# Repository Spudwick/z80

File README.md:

# z80

Repository for all things related to z80 project. Makefile supports both windows and linux!

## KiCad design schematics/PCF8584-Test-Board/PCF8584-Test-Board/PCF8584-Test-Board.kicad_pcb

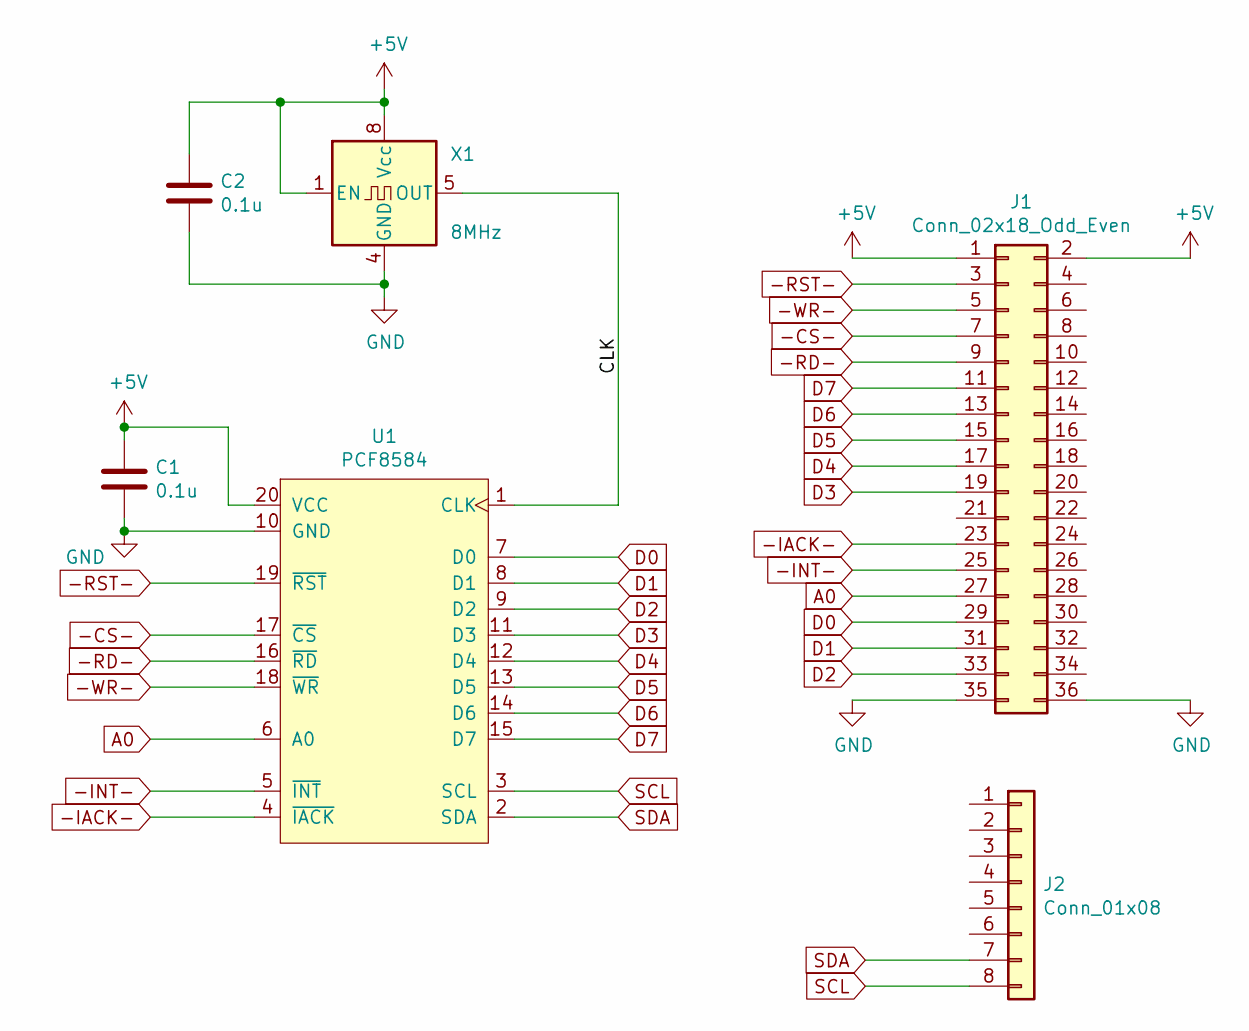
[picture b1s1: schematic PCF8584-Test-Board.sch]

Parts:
C1, C2: 0.1u; C_0603_1608Metric_Pad1.05x0.95mm_HandSolder
J1: Conn_02x18_Odd_Even; PinHeader_2x18_P2.54mm_Vertical
J2: Conn_01x08; PinHeader_1x08_P2.54mm_Vertical
U1: PCF8584; SOIC-20W_7.5x12.8mm_P1.27mm
X1: 8MHz; Oscillator_DIP-8

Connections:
+5V: C1.1, C2.1, J1.1, J1.2, U1.20 (VCC), X1.1 (EN), X1.8 (Vcc)
-CS-: J1.7, U1.17 (~CS)
-IACK-: J1.23, U1.4 (~IACK)
-INT-: J1.25, U1.5 (~INT)
-RD-: J1.9, U1.16 (~RD)
-RST-: J1.3, U1.19 (~RST)
-WR-: J1.5, U1.18 (~WR)
/CLK: U1.1 (CLK), X1.5 (OUT)
A0: J1.27, U1.6 (A0)
D0: J1.29, U1.7 (D0)
D1: J1.31, U1.8 (D1)
D2: J1.33, U1.9 (D2)
D3: J1.19, U1.11 (D3)
D4: J1.17, U1.12 (D4)
D5: J1.15, U1.13 (D5)
D6: J1.13, U1.14 (D6)
D7: J1.11, U1.15 (D7)
GND: C1.2, C2.2, J1.35, J1.36, U1.10 (GND), X1.4 (GND)
SCL: J2.8, U1.3 (SCL)
SDA: J2.7, U1.2 (SDA)

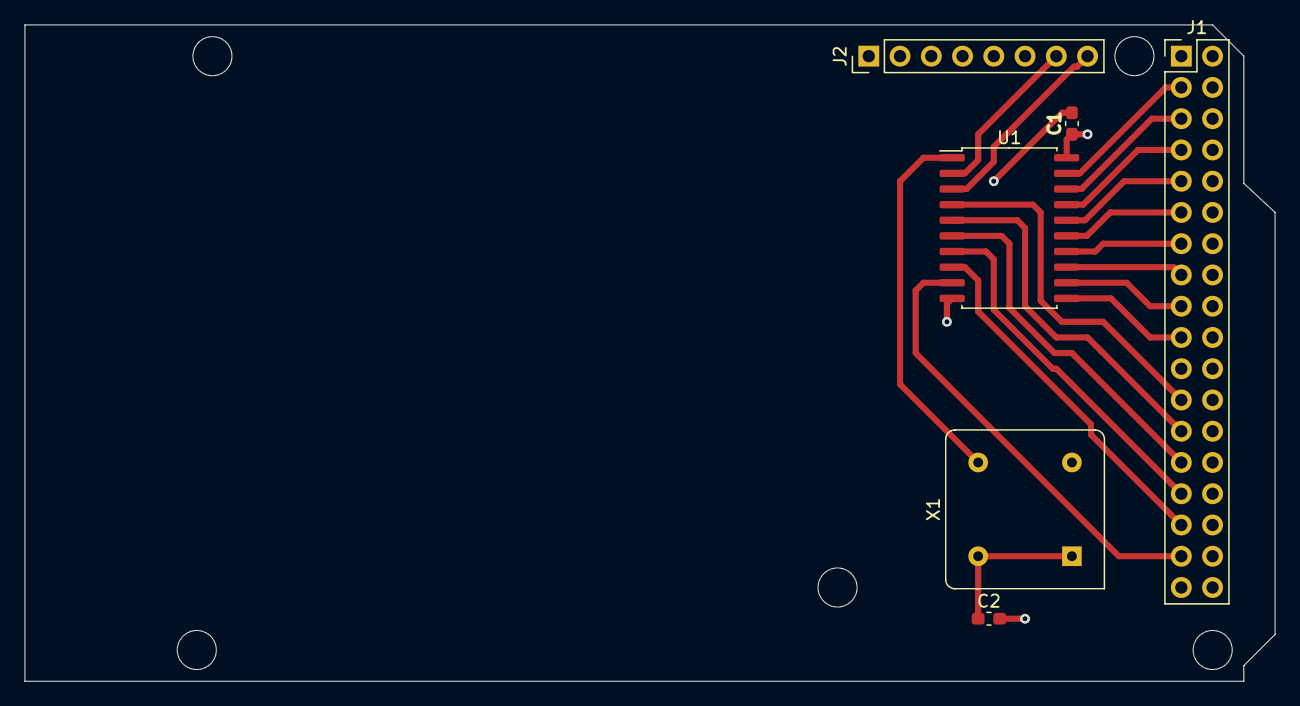
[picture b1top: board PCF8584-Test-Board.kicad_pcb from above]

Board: 2 copper layers, 101.6 x 53.3 mm, 6 parts (0 on the bottom side), 20 nets.

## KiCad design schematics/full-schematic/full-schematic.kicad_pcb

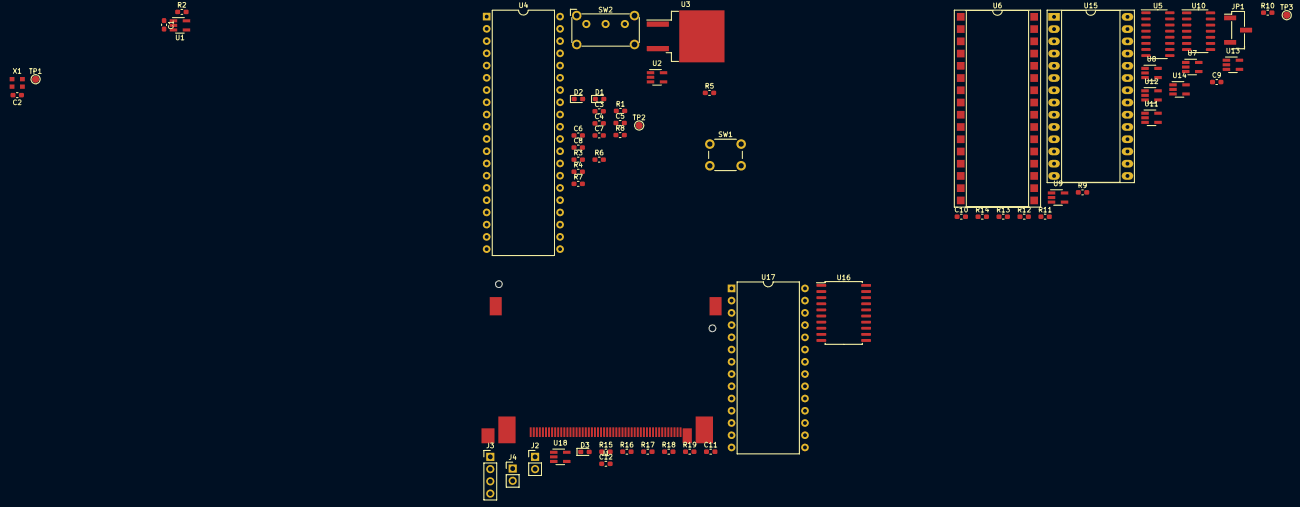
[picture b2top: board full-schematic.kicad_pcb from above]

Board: 2 copper layers, 63 parts (0 on the bottom side), 77 nets, no tracks yet.

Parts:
C1, C2, C3, C4, C7, C8, C9, C10, C11, C12: 0.1u; C_0603_1608Metric_Pad1.05x0.95mm_HandSolder
C5, C6: 1m; C_0603_1608Metric_Pad1.05x0.95mm_HandSolder
D1: D_Schottky; D_0603_1608Metric_Pad1.05x0.95mm_HandSolder
D2, D3: LED; LED_0603_1608Metric_Pad1.05x0.95mm_HandSolder
J1: Conn_02x25_Top_Bottom; Molex_553595029_CF_Socket
J2, J4: Conn_01x02; PinHeader_1x02_P2.54mm_Vertical
J3: Conn_01x04; PinHeader_1x04_P2.54mm_Vertical
JP1: Jumper_NC_Dual; PinHeader_1x03_P2.54mm_Vertical_SMD_Pin1Left
R1: 100k; R_0603_1608Metric_Pad1.05x0.95mm_HandSolder
R2, R3: 10k; R_0603_1608Metric_Pad1.05x0.95mm_HandSolder
R4: 330; R_0603_1608Metric_Pad1.05x0.95mm_HandSolder
R5, R6, R7, R8, R9, R10, R11, R12, R13, R14, R15, R16, R17, R18, R19: 1k; R_0603_1608Metric_Pad1.05x0.95mm_HandSolder
SW1: SW_Push_Dual; SW_PUSH_6mm
SW2: SW_SPST; SW_E-Switch_EG1224_SPDT_Angled
TP1, TP2, TP3: TestPoint_Probe; TestPoint_Pad_D1.5mm
U1: LP3470; SOT-23-5_HandSoldering
U2, U9: 74LVC1G08; SOT-23-5_HandSoldering
U3: L7805; TO-263-2
U4: Z80CPU; DIP-40_W15.24mm
U5: 74LS138; SOIC-16_3.9x9.9mm_P1.27mm
U6: CY62128ELL-45SXI; DIP-32_W15.24mm_SMDSocket_SmallPads
U7, U8, U11, U13, U14: 74LVC1G32; SOT-23-5_HandSoldering
U10: 74HC107D; SOIC-14_3.9x8.7mm_P1.27mm
U12, U18: 74LVC1G04; SOT-23-5_HandSoldering
U15: AT28C256-15PU; DIP-28_W15.24mm_Socket_LongPads
U16: PCF8584; SOIC-20W_7.5x12.8mm_P1.27mm
U17: CP82C52Z; DIP-28_W15.24mm
X1: XO32; Oscillator_SMD_EuroQuartz_XO32-4Pin_3.2x2.5mm

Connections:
+5V: C2.1, C6.1, C7.1, C8.1, C9.1, C10.1, C11.1, C12.1, J1.13, J1.38, R1.2, R2.2, R4.1, R5.1, R6.1, R7.1, R8.1, R9.2, R10.2, R12.1, R14.1, R15.1, R16.1, R17.1, R18.1, R19.1, U1.3, U1.4, U2.5, U3.3, U4.11, U5.16, U6.8, U7.5, U8.5, U9.5, U11.5, U12.5, U13.5, U14.5, U15.28, U16.20, U17.27, U18.5, X1.1, X1.4
-CFCS-: J1.7, U5.13
-I2CCS-: U5.15, U16.17
-IORQ-: U4.20, U5.4, U5.5
-MREQ-: U4.19, U13.2, U14.1
-RAMCS-: U6.30, U14.4
-RD-: J1.34, U4.21, U6.32, U8.2, U15.22, U16.16, U17.1
-ROMCS-: U13.4, U15.20
-RST-: J1.41, TP2.1, U2.4, U4.26, U9.2, U16.19, U18.2
-UARTCS-: U5.14, U17.28
-WR-: J1.35, JP1.1, U4.22, U6.5, U7.2, U16.18, U17.2
/Sheet1/-POR-: R2.1, U1.5, U2.1
/Sheet2/ROM_DIS: TP3.1, U10.3, U11.1
/Sheet3/-CF_ACT-: D3.1, J1.45
A0: J1.20, U4.30, U6.20, U15.10, U16.6, U17.11
A1: J1.19, U4.31, U6.19, U15.9, U17.12
A2: J1.18, U4.32, U6.18, U15.8
A3: U4.33, U6.17, U15.7
A4: U4.34, U6.16, U15.6
A5: U4.35, U5.1, U6.15, U15.5
A6: U4.36, U5.2, U6.14, U15.4
A7: U4.37, U5.3, U6.13, U15.3
A8: U4.38, U6.3, U15.25
A9: U4.39, U6.2, U15.24
A10: U4.40, U6.31, U15.21
A11: U4.1, U6.1, U15.23
A12: U4.2, U6.12, U15.2
A13: U4.3, U6.4, U15.26
A14: U4.4, U6.11, U15.1
A15: U4.5, U6.7, U11.2
D0: J1.21, U4.14, U6.21, U15.11, U16.7, U17.3
D1: J1.22, U4.15, U6.22, U15.12, U16.8, U17.4
D2: J1.23, U4.12, U6.23, U15.13, U16.9, U17.5
D3: J1.2, U4.8, U6.25, U15.15, U16.11, U17.6
D4: J1.3, U4.7, U6.26, U15.16, U16.12, U17.7
D5: J1.4, U4.9, U6.27, U15.17, U16.13, U17.8
D6: J1.5, U4.10, U6.28, U15.18, U16.14, U17.9
D7: J1.6, U4.13, U6.29, U15.19, U16.15, U17.10
GND: C1.2, C2.2, C3.2, C4.2, C5.2, C6.2, C7.2, C8.2, C9.2, C10.2, C11.2, C12.2, D2.1, J1.1, J1.8, J1.9, J1.10, J1.11, J1.12, J1.14, J1.15, J1.16, J1.17, R11.2, R13.2, SW1.1, U1.2, U2.3, U3.2, U4.29, U5.8, U6.24, U7.3, U8.3, U9.3, U11.3, U12.3, U13.3, U14.3, U15.14, U16.10, U17.16, U18.3, X1.2
unnamed: C1.1, U1.1
unnamed: C3.1, C5.1, SW2.2, U3.1
unnamed: C4.1, R3.1, U2.2
unnamed: D1.1, SW2.1
unnamed: D2.2, R4.2
unnamed: D3.2, R18.2
unnamed: J1.32, R15.2
unnamed: J1.36, R16.2
unnamed: J1.44, R17.2
unnamed: J1.46, R19.2
unnamed: J3.1, U17.20
unnamed: J3.2, U17.19
unnamed: J3.3, U17.18
unnamed: J3.4, U17.17
unnamed: J4.1, U17.25
unnamed: J4.2, U17.15
unnamed: JP1.2, U15.27
unnamed: JP1.3, R14.2
unnamed: R1.1, R3.2, SW1.2
unnamed: R5.2, U4.17
unnamed: R6.2, U4.16
unnamed: R7.2, U4.24
unnamed: R8.2, U4.25
unnamed: R9.1, U5.6
unnamed: R10.1, U6.6
unnamed: R11.1, U6.10
unnamed: R12.2, U10.1
unnamed: R13.1, U10.4
unnamed: U5.7, U7.1, U8.1
unnamed: U8.4, U9.1
unnamed: U7.4, U10.12
unnamed: U9.4, U10.13
unnamed: U11.4, U12.2, U13.1
unnamed: U12.4, U14.2
unnamed: U17.23, U18.4
SCL: J2.1, U16.3
SDA: J2.2, U16.2
SYS_CLK: TP1.1, U4.6, U16.1, U17.13, X1.3

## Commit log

2018-03-03 Adding files and folders to repository
2018-03-03 Removed output directories
2018-03-03 Removed sub make files dependance on location
2018-03-03 Repo restructure
2018-03-03 Deleted folders left after restructure
2018-03-03 Added memory map excel file
2018-03-03 Moved Memory_Map.ods to docs folder
2018-03-03 Renamed z80std library to z80core
2018-05-16 Misc
    Miscelaneous changes
2018-05-17 Makefile changes
    Modified individual makefiles to set variables that then get incorporated in the main makefile.
2018-05-17 Windows Support
    Started adding support to makefile for windows building.
2018-05-18 Windows build support
    Finished adding support for building on windows.
    Still need to check that Linux building hasn't broken.
2018-05-18 Addition of Make exe to repository
    Added make executable to repository.
2018-05-19 Completed windows support
    Almost fully working windows support. Still need to find a objcopy alternative for windows.
2018-05-19 Full windows support
    Removed source code for make.
    Added hex2bin for binary creation on windows.
    Still need to retest linux build to ensure hasn't been broken.
2018-05-19 Small changes
    Alignment changes mostly.
2018-05-20 Modified makefile to allow fedora linux to build.
2018-05-20 Testing git user
2018-05-20 Testing git email
2018-05-20 Added an ignore rule to prevent output directories from being uploaded.
2018-05-21 Comments + Binary out location
    Mainly adding comments to makefile.
    Also added in a move command to windows case to get around hex2bin producing binary in same folder as ihx.
2018-05-21 Rearrangements
    Rearranged makefile so tools are all grouped.
    Also prevent windows mkdir from erroring if folder already exists.
2018-05-21 Library test
    Check to make sure libraries can still be included.
2018-05-21 Error trap
    Added a trap to trigger an error if target isn't specified.
2018-05-22 Small modification
    Modified library info printout to use os specific syntax for directories.
2018-06-01 Custom standard library
    Inclusion of modified SDCC standard c library. Required modification as z80.lib built for specific machine therefore included a definition of putchar. Also added a printf test.
2018-06-01 Printf corrections
    corrections to allow printf to be used.
2018-06-03 Started UART library
    Started writing uart library for SCC2691.
2018-06-04 SCC2691 library changes
2018-06-05 Re-jig of library building
    Changed how library building copies over header files.
2018-06-05 Changes to library building
2018-06-07 Compilation area changed
    Changed how areas are defined for compilation. Stops linker throwing errors due to area definitions being included that don't have code to be loaded.
2018-06-07 SCC2691 Basic functionality
    basic functionality of SCC2691 completed. Added trap functionality.
2018-06-08 Commenting
2018-06-11 Misc changes
2018-06-12 Added C_AREA
2018-06-13 Addition of tools
    Added Graphviz
    Added Radare2
2018-06-18 Small changes
    Nothing important
2018-06-18 Makefile tests
    playing around with ideas for enabling code segs to be set for specific files.
2018-06-19 New build system started
    Started playing with ideas for new build system.
2018-08-14 Small changes
2018-08-14 More small changes
2018-08-15 Basic functionality
2018-08-15 Multi-module building
2018-08-16 Mainly comments
2018-08-16 Generating .dep files
2018-08-16 Seperate Preprocessing
    Moved preprocessing stage to it's own rule for greater compilation control.
2018-08-16 IHX Linking stage added
    IHX linking stage added with checks to see if it's a multiple module link or single module.
2018-08-16 Binary creation added
    Added creation of binary file from ihx file. Still work in progress as linker is left to choose area locations.
2018-08-16 Linux Support
2018-08-20 Code areas
2018-08-20 Added missing mem_map.mk file
2018-08-20 Added other code areas
2018-08-21 Completed multi-platform support
2018-08-21 Misc
2018-11-06 Misc stuff
2018-12-03 Library Building
    Modifications to allow building of sdcc libraries.
2018-12-04 Library building and including
    Made changes to how libraries are built, updated standard library and modified how libraries are included in a modules build process.
2018-12-04 Library Updates
2018-12-14 Updated libraries
    Brought all libraries up to latest build-sys format.
2018-12-21 Bootloader
2019-02-22 General Updates
    Updated build system comments. Had a play with calling into program memory using Memory Map table in info.s.
2019-02-22 Updates to info.s
    Updates to the info data in the bootloader. Would like to have authors name too but run out of available space.
2019-03-14 Datasheets
    Added datasheets directory.
2019-03-14 UART Stuff
    Added extra uart stuff.
2019-03-14 General build system updates. Also made some linux specific changes and added system library support.
2019-03-15 Windows updates
    Probably broken linux now XD
2019-05-29 Rel building
2019-06-05 Partial bookin of changes
2019-06-07 Added BOMs Directory
    Added BOM directory and create initial BOM for basic setup.
2019-06-13 Multi-tasking
    started toying with multi-tasking ideas.
2019-06-14 more plays with multi-task
2019-06-17 Context Switching tests
2019-06-18 context loading
    Renaming and new context loading
2019-06-19 stuff
2019-08-04 Added schematics
2019-08-04 Added full schematic version
2019-08-12 More sims
    Logic simulation stuffs
2019-08-13 Complete turnaround
2019-08-13 Missing folders
2019-08-15 More dev
2019-10-23 not sure
2019-10-24 Restarted Development
2019-10-25 First working iteration
2019-10-28 Started Code Seqments
2019-10-28 New database build.
2019-10-30 .gitignore updates
2019-10-31 Initial clean
2019-11-29 Started elf tools
2019-12-18 Schematics
2019-12-19 Schematic updates
2019-12-19 Datasheet
2020-01-17 Completed rule generation from database
2020-01-17 Comments in database
2020-01-22 Additional files and some segment work
2020-01-22 Begining libraries and .PHONY rules
2020-01-22 Added files to .gitignore
2020-01-23 Defines and Beginnings of Libraries
2020-02-03 Segments
2020-02-08 removed merge residuals
2020-02-10 Begun ZOS development
2020-02-11 Started UART chip arduino tests.
2020-02-12 Removed double folder
2020-02-12 Added Bus_Utilities arduino library
